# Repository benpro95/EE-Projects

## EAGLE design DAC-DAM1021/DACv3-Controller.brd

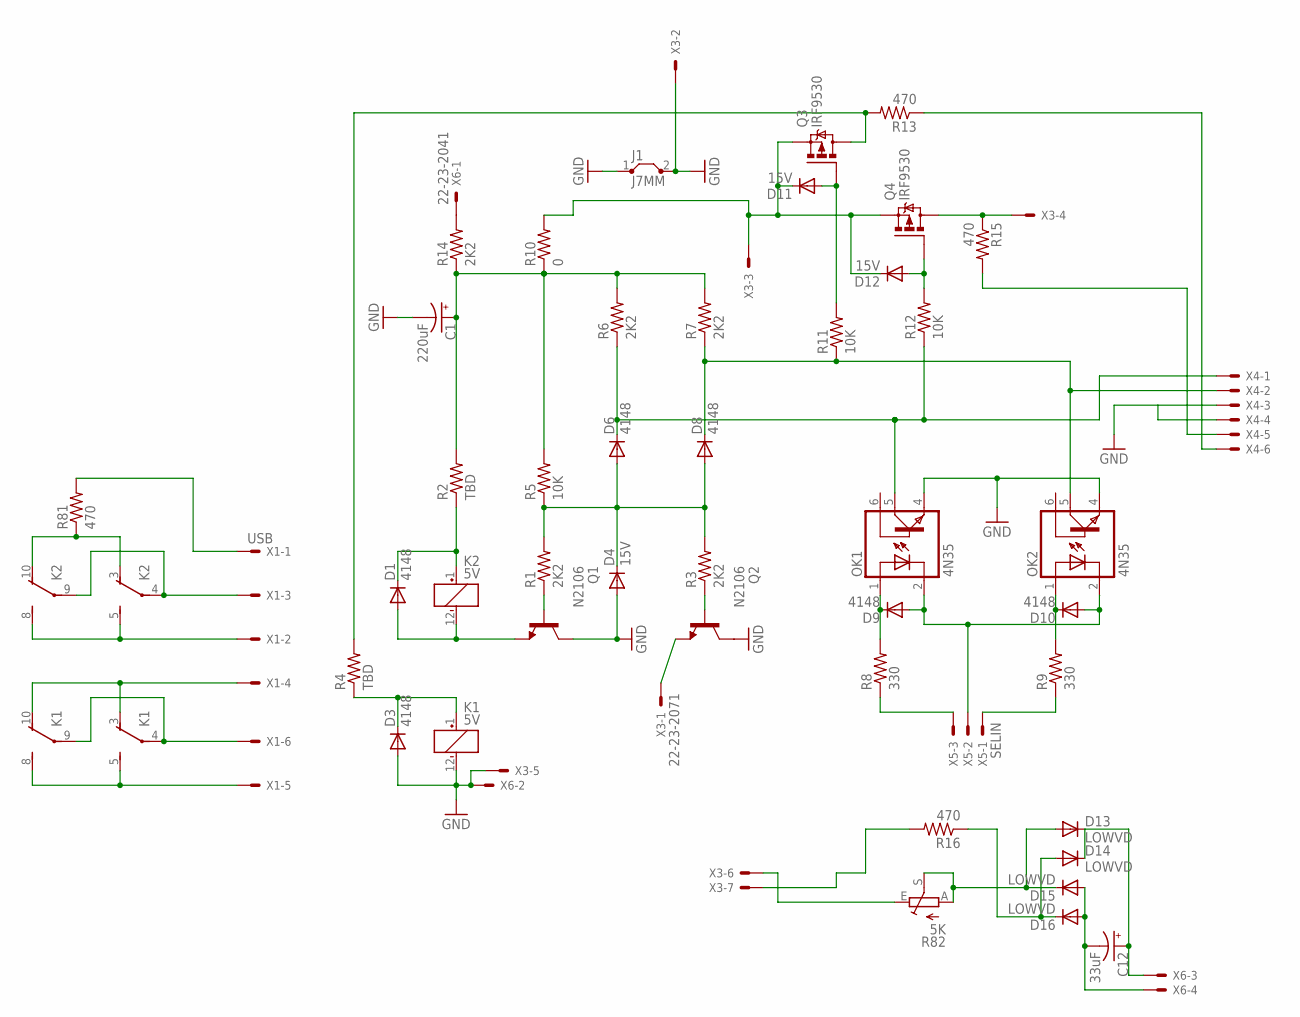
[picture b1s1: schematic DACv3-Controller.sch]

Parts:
C1: 220uF; E5-10,5
C12: 33uF; TAP5-60
D1, D3, D6, D8, D9, D10: 4148; DO35-7
D4, D11, D12: 15V; DO35-7
D13, D14, D15, D16: LOWVD; DO35-7
J1: J7MM; 07
K1, K2: 5V; TX2; MPN TX2-12V
OK1, OK2: 4N35; DIL06
Q1, Q2: N2106; TO92-EBC
Q3, Q4: IRF9530; TO220BV
R1, R3, R6, R7: 2K2; 0207/10
R2, R4: TBD; 0207/10
R5, R11, R12: 10K; 0207/10
R8, R9: 330; 0207/10
R10: 0; 0207/12
R13, R15, R16, R81: 470; 0207/10
R14: 2K2; 0207/12
R82: 5K; RJ9W
X1: USB; 22-23-2061
X3: 22-23-2071
X4: 22-23-2061
X5: SELIN; 22-23-2031
X6: 22-23-2041

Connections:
GND: C1.-, D3.A, D4.A, J1.1, J1.2, K1.12 (-), OK1.4 (EMI), OK2.4 (EMI), Q1.C, Q2.C, X3.2, X3.5, X4.3, X4.4, X6.2
unnamed: K2.4, K2.9, X1.3
unnamed: K2.3 (O), K2.10 (O), R81.1
unnamed: K2.5 (S), K2.8 (S), X1.2
unnamed: R81.2, X1.1
unnamed: K1.4, K1.9, X1.6
unnamed: K1.3 (O), K1.10 (O), X1.4
unnamed: K1.5 (S), K1.8 (S), X1.5
unnamed: D3.C, K1.1 (+), R4.1
unnamed: R8.1, X5.3
unnamed: D1.A, K2.12 (-), Q1.E
unnamed: D1.C, K2.1 (+), R2.1
unnamed: Q1.B, R1.1
unnamed: Q2.B, R3.1
unnamed: D4.C, D6.A, D8.A, R1.2, R3.2, R5.1
unnamed: Q2.E, X3.1
unnamed: D6.C, OK1.5 (COL), R6.1, R12.1, X4.1
unnamed: D8.C, OK2.5 (COL), R7.1, R11.1, X4.2
unnamed: C1.+, R2.2, R5.2, R6.2, R7.2, R10.1, R14.1
unnamed: D9.A, D10.A, OK1.2 (C), OK2.2 (C), X5.2
unnamed: D10.C, OK2.1 (A), R9.2
unnamed: D9.C, OK1.1 (A), R8.2
unnamed: R9.1, X5.1
unnamed: D11.A, Q3.G, R11.2
unnamed: D12.A, Q4.G, R12.2
unnamed: D11.C, D12.C, Q3.S, Q4.S, R10.2, X3.3
unnamed: Q3.D, R4.2, R13.2
unnamed: Q4.D, R15.1, X3.4
unnamed: R15.2, X4.5
unnamed: R13.1, X4.6
unnamed: R82.E, X3.6
unnamed: R16.2, X3.7
unnamed: D14.A, D16.C, R16.1
unnamed: D13.A, D15.C, R82.A, R82.S
unnamed: R14.2, X6.1
unnamed: C12.-, D15.A, D16.A, X6.4
unnamed: C12.+, D13.C, D14.C, X6.3

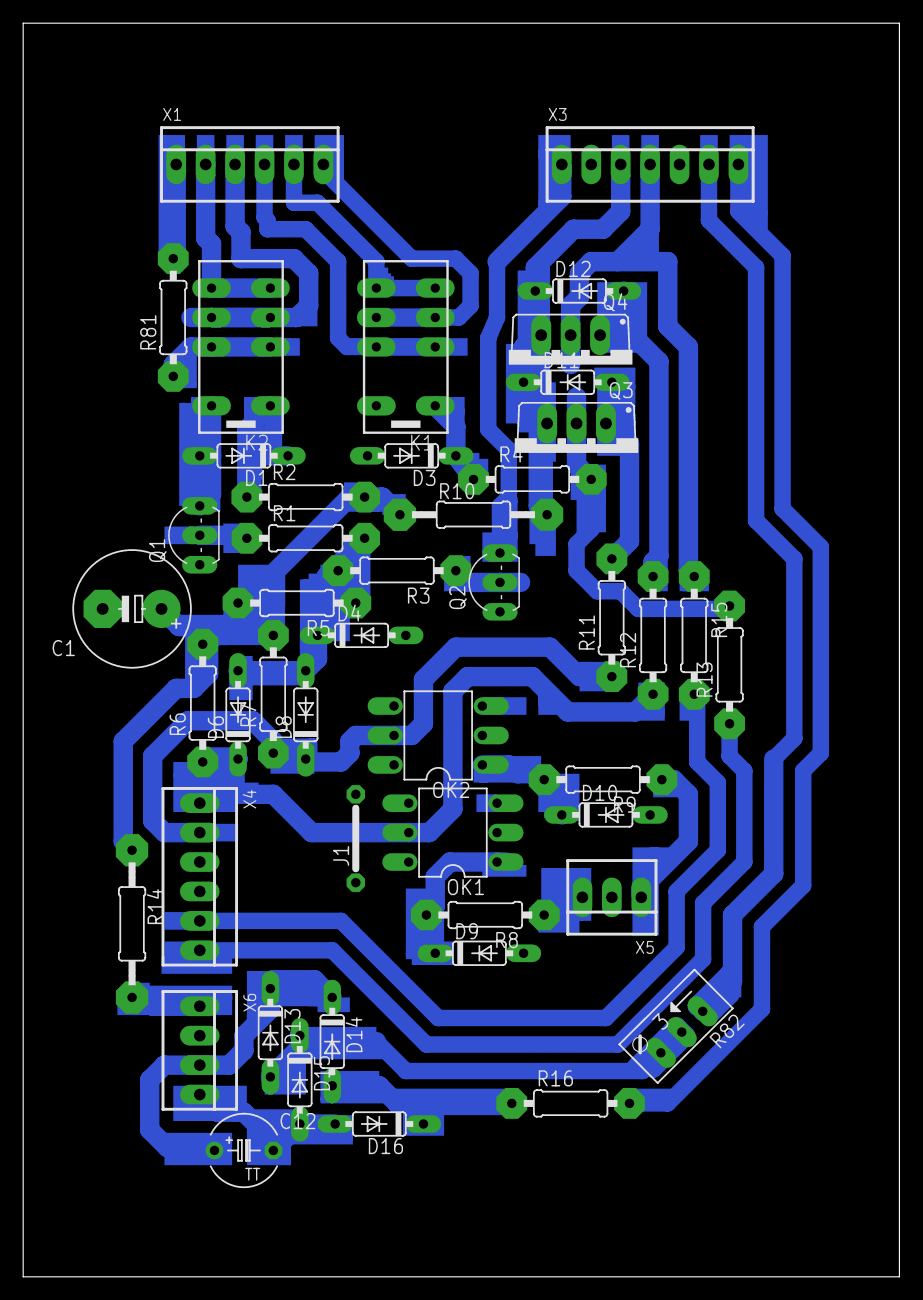
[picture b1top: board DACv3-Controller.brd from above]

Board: 2 copper layers, 75.6 x 108.2 mm, 47 parts (0 on the bottom side), 37 nets.

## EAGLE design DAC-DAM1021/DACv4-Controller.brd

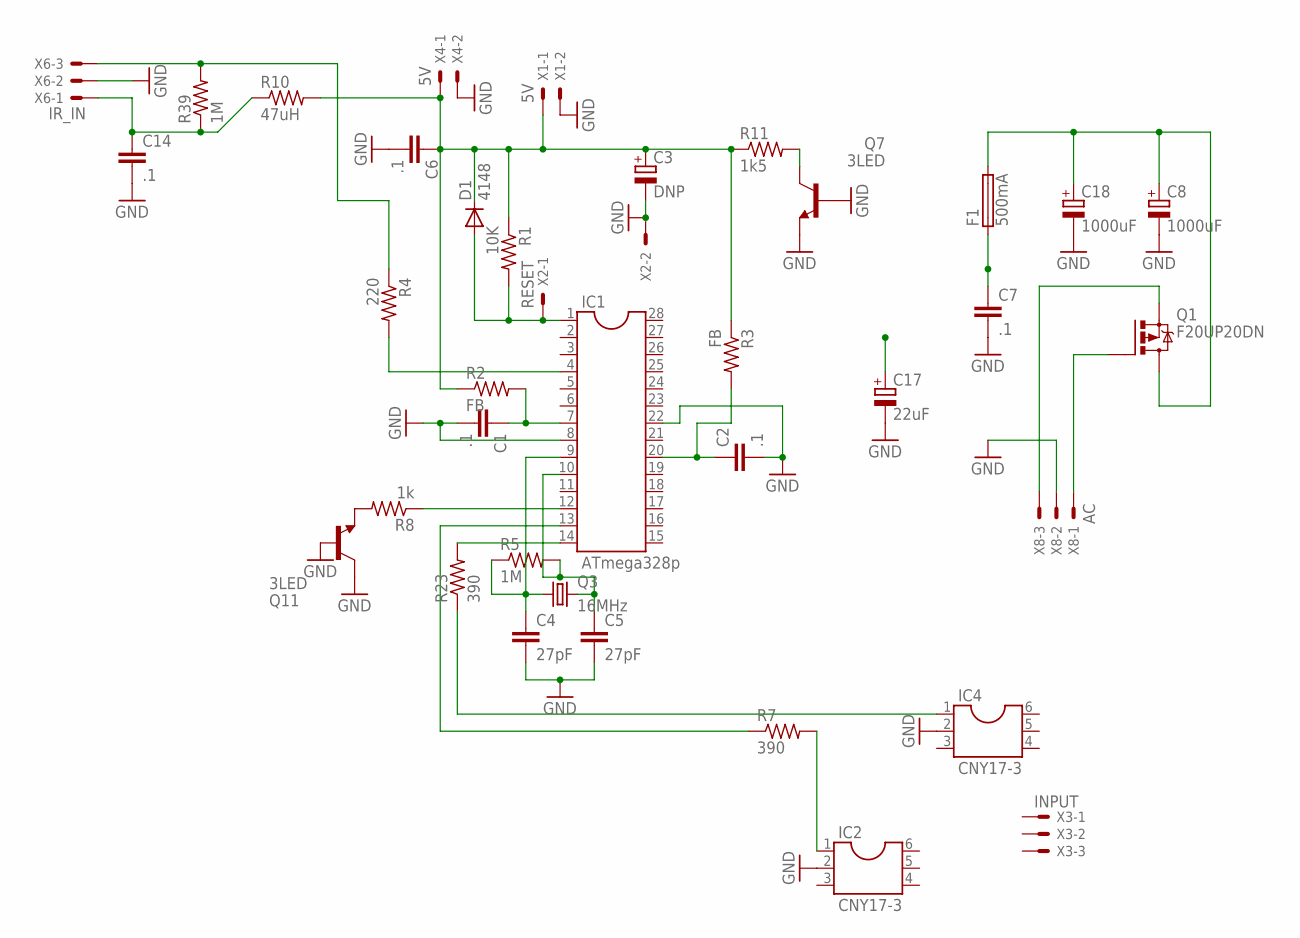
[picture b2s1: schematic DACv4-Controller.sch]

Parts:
C1, C2, C6, C7, C14: .1; C1210K
C3: DNP; E3,5-10
C4, C5: 27pF; C1210K
C8, C18: 1000uF; E5-13
C17: 22uF; E3,5-10
D1: 4148; DO35-7
F1: 500mA; 19560
IC1: ATmega328p; DIL28-3
IC2, IC4: CNY17-3; DIL06
Q1: F20UP20DN; TO220BV
Q3: 16MHz; HC49/S
Q7, Q11: 3LED; TO92-EBC
R1: 10K; 0309/10
R2: FB; 0309/10
R3: FB; 0309/12
R4: 220; 0309/12
R5: 1M; 0309V
R7, R23: 390; 0309/10
R8: 1k; 0204/7
R10: 47uH; 0309/10
R11: 1k5; 0309/12
R39: 1M; 0309/10
X1, X4: 5V; 22-23-2021
X2: RESET; 22-23-2021
X3: INPUT; 22-23-2031
X6: IR_IN; 22-23-2031
X8: AC; 22-23-2031

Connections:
GND: C1.2, C2.2, C3.-, C4.2, C5.2, C6.2, C7.2, C8.-, C14.2, C17.-, C18.-, IC1.8, IC1.22, IC2.2, IC4.2, Q7.B, Q7.E, Q11.B, Q11.C, X1.2, X2.2, X4.2, X6.2, X8.2
unnamed: IC2.1, R7.2
unnamed: D1.A, IC1.1, R1.2, X2.1
unnamed: IC1.4, R4.2
unnamed: C2.1, IC1.20, R3.2
unnamed: R4.1, R39.2, X6.3
unnamed: IC1.13, R7.1
unnamed: IC1.12, R8.1
unnamed: C4.1, IC1.9, Q3.1, R5.1
unnamed: C5.1, IC1.10, Q3.2, R5.2
unnamed: C7.1, F1.1
unnamed: C14.1, R10.1, R39.1, X6.1
unnamed: Q7.C, R11.2
unnamed: C8.+, C18.+, F1.2, Q1.D
unnamed: Q1.S, X8.3
unnamed: Q1.G, X8.1
unnamed: C3.+, C6.1, D1.C, R1.1, R2.1, R3.1, R10.2, R11.1, X1.1, X4.1
unnamed: C1.1, IC1.7, R2.2
unnamed: IC1.14, R23.2
unnamed: IC4.1, R23.1
unnamed: Q11.E, R8.2

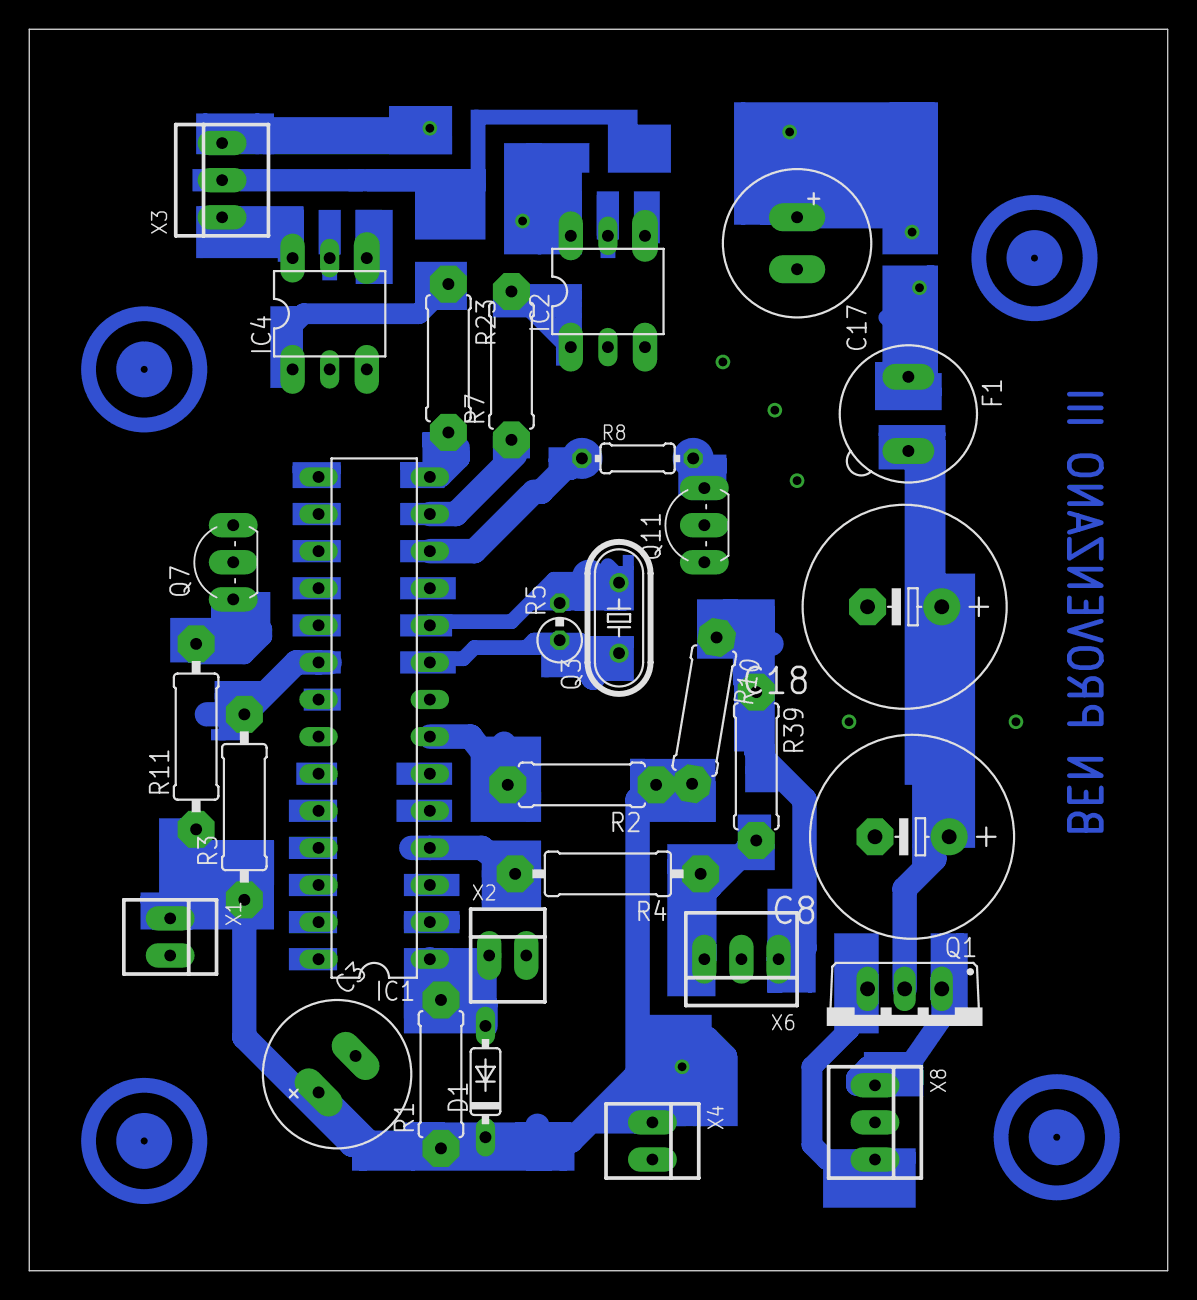
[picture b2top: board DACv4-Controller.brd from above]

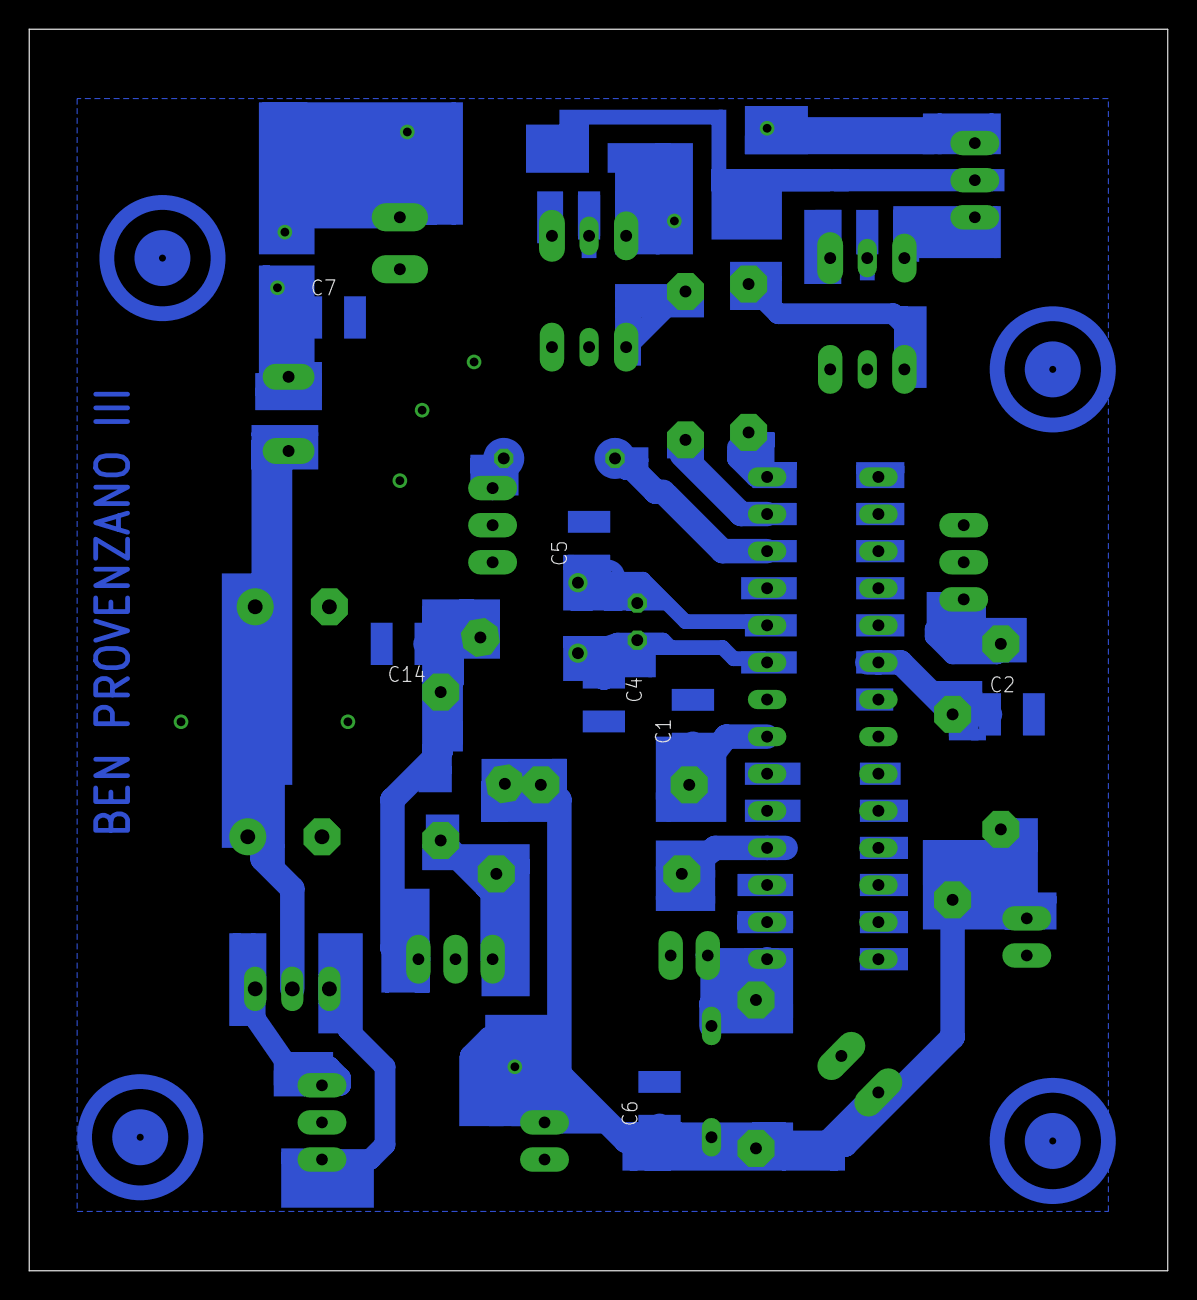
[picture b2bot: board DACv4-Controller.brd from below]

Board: 2 copper layers, 78.0 x 85.0 mm, 37 parts (7 on the bottom side), 21 nets.

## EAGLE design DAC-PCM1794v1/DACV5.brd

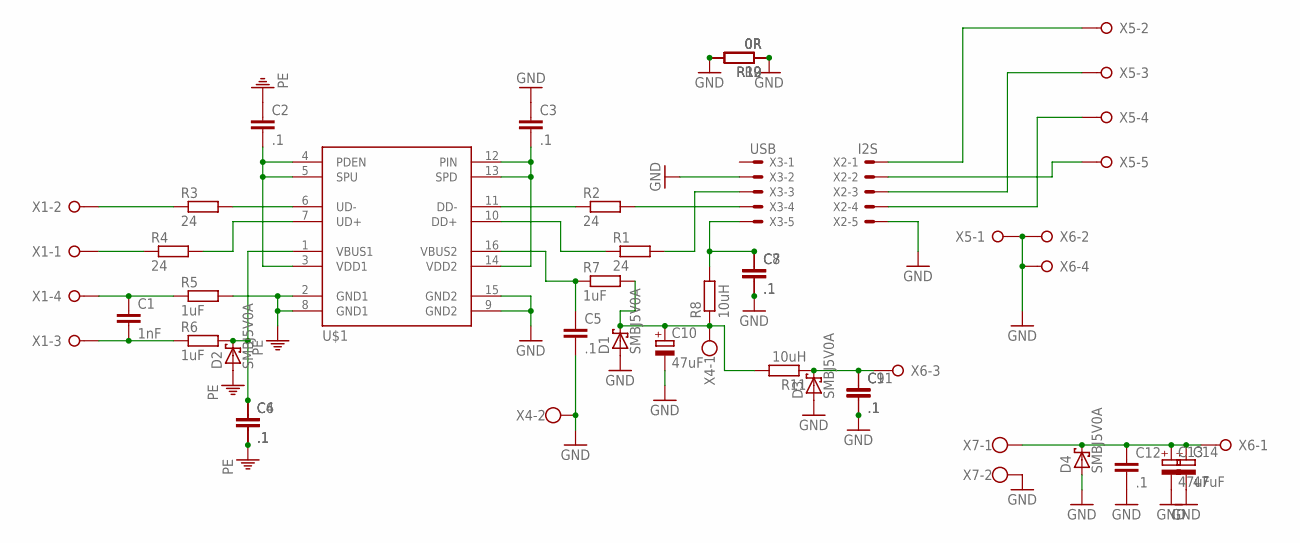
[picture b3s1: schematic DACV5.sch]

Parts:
C1: 1nF; C1210
C2, C3, C4, C5, C6, C7, C8, C9, C11, C12: .1; C1210
C10, C13, C14: 47uF; E5-13
D1, D2, D3, D4: SMBJ5V0A; SMB
R1, R2, R3, R4: 24; R1210
R5, R6, R7: 1uF; R1210
R8, R11: 10uH; 0309/12
R9, R10, R12: 0R; 0309/12
U$1: ADUM4160; SO16W
X1, X6: W237-04P; W237-4P
X2: I2S; 22-23-2051
X3: USB; 22-23-2051
X4: W237-102
X5: W237-05P; W237-5P
X7: W237-102; MPN 237-102

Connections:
GND: C3.1, C5.2, C7.2, C8.2, C9.2, C10.-, C11.2, C12.2, C13.-, C14.-, D1.A, D3.A, D4.A, R9.1, R9.2, R10.1, R10.2, R12.1, R12.2, U$1.9 (GND2), U$1.15 (GND2), X2.5, X3.2, X4.2, X5.1, X6.2, X6.4, X7.2
unnamed: X2.1, X5.2
unnamed: R1.2, X3.3
unnamed: R1.1, U$1.10 (DD+)
unnamed: R4.1, X1.1
unnamed: R3.1, X1.2
unnamed: R2.1, U$1.11 (DD-)
unnamed: R2.2, X3.4
unnamed: R3.2, U$1.6 (UD-)
unnamed: R4.2, U$1.7 (UD+)
unnamed: C1.1, R5.1, X1.4
unnamed: C1.2, R6.1, X1.3
unnamed: C10.+, D1.C, R7.2, R8.1, R11.2, X4.1
unnamed: C7.1, C8.1, R8.2, X3.5
unnamed: X2.3, X5.3
unnamed: X2.2, X5.5
unnamed: X2.4, X5.4
unnamed: C9.1, C11.1, D3.C, R11.1, X6.3
unnamed: C12.1, C13.+, C14.+, D4.C, X6.1, X7.1
PE: C2.1, C4.2, C6.2, D2.A, R5.2, U$1.2 (GND1), U$1.8 (GND1)
VBUS1: C4.1, C6.1, D2.C, R6.2, U$1.1 (VBUS1)
VBUS2: C5.1, R7.1, U$1.16 (VBUS2)
VDD1: C2.2, U$1.3 (VDD1), U$1.4 (PDEN), U$1.5 (SPU)
VDD2: C3.2, U$1.12 (PIN), U$1.13 (SPD), U$1.14 (VDD2)

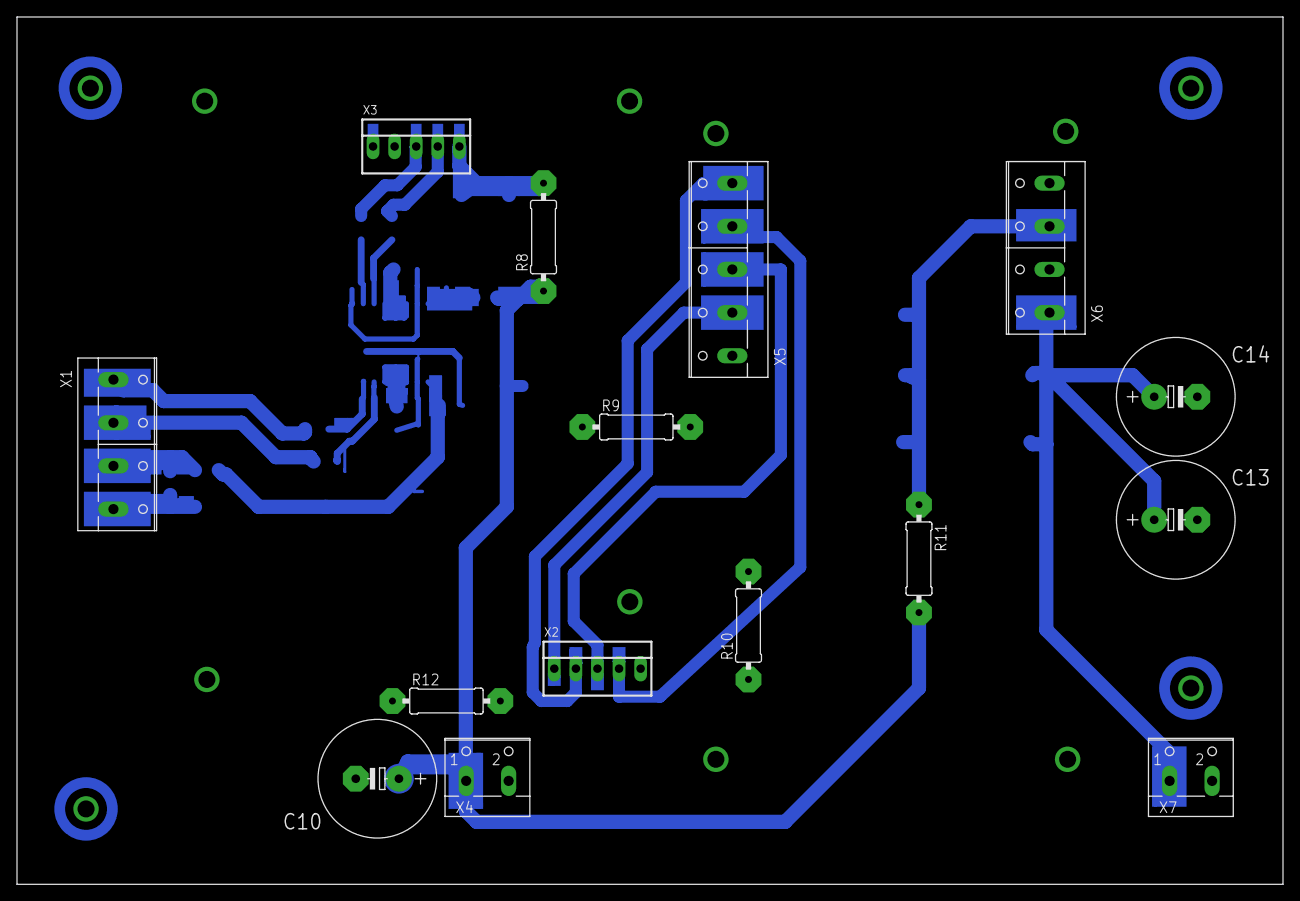
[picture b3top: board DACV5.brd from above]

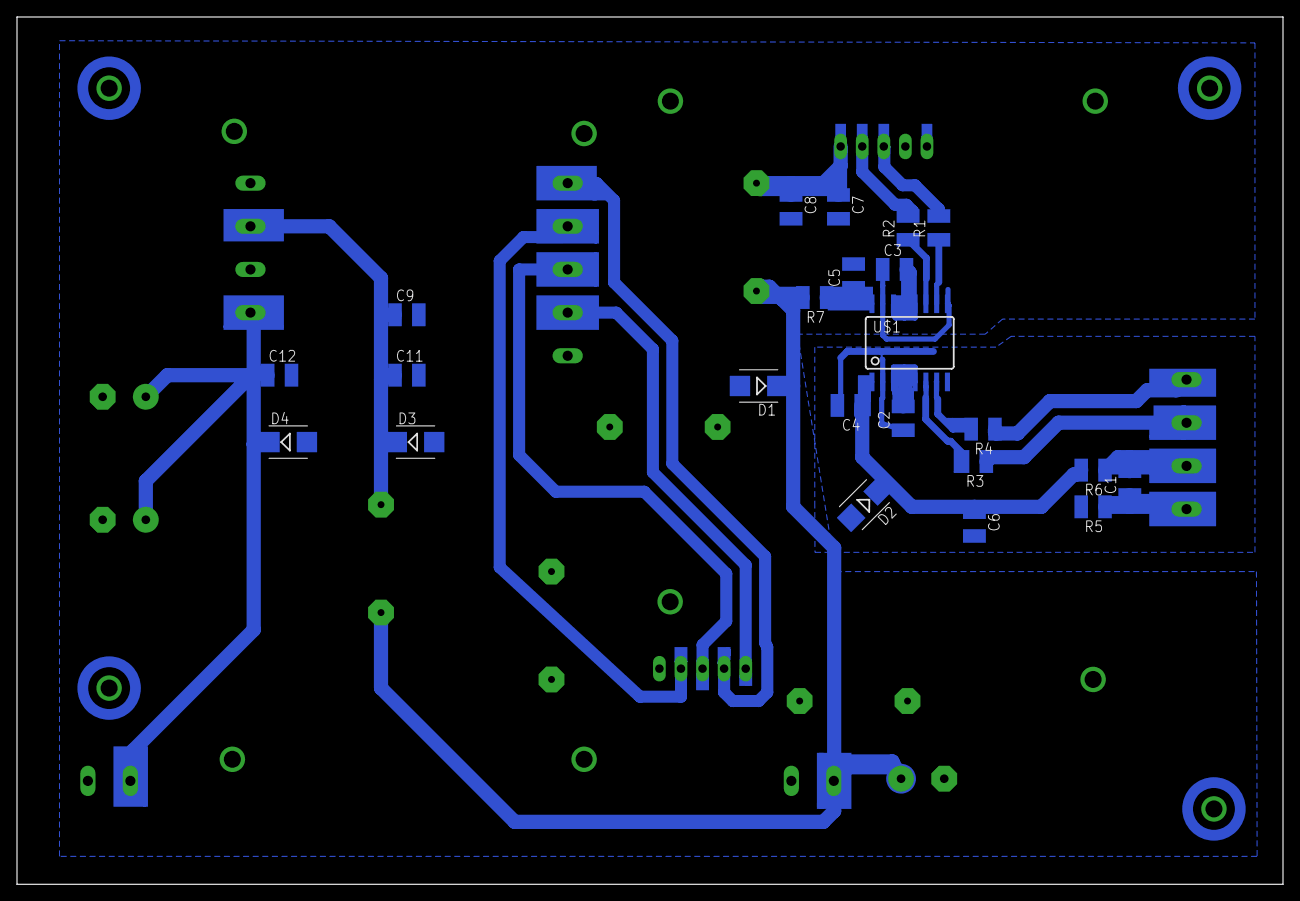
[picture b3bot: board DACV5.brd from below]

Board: 2 copper layers, 149.0 x 102.1 mm, 38 parts (23 on the bottom side), 24 nets.

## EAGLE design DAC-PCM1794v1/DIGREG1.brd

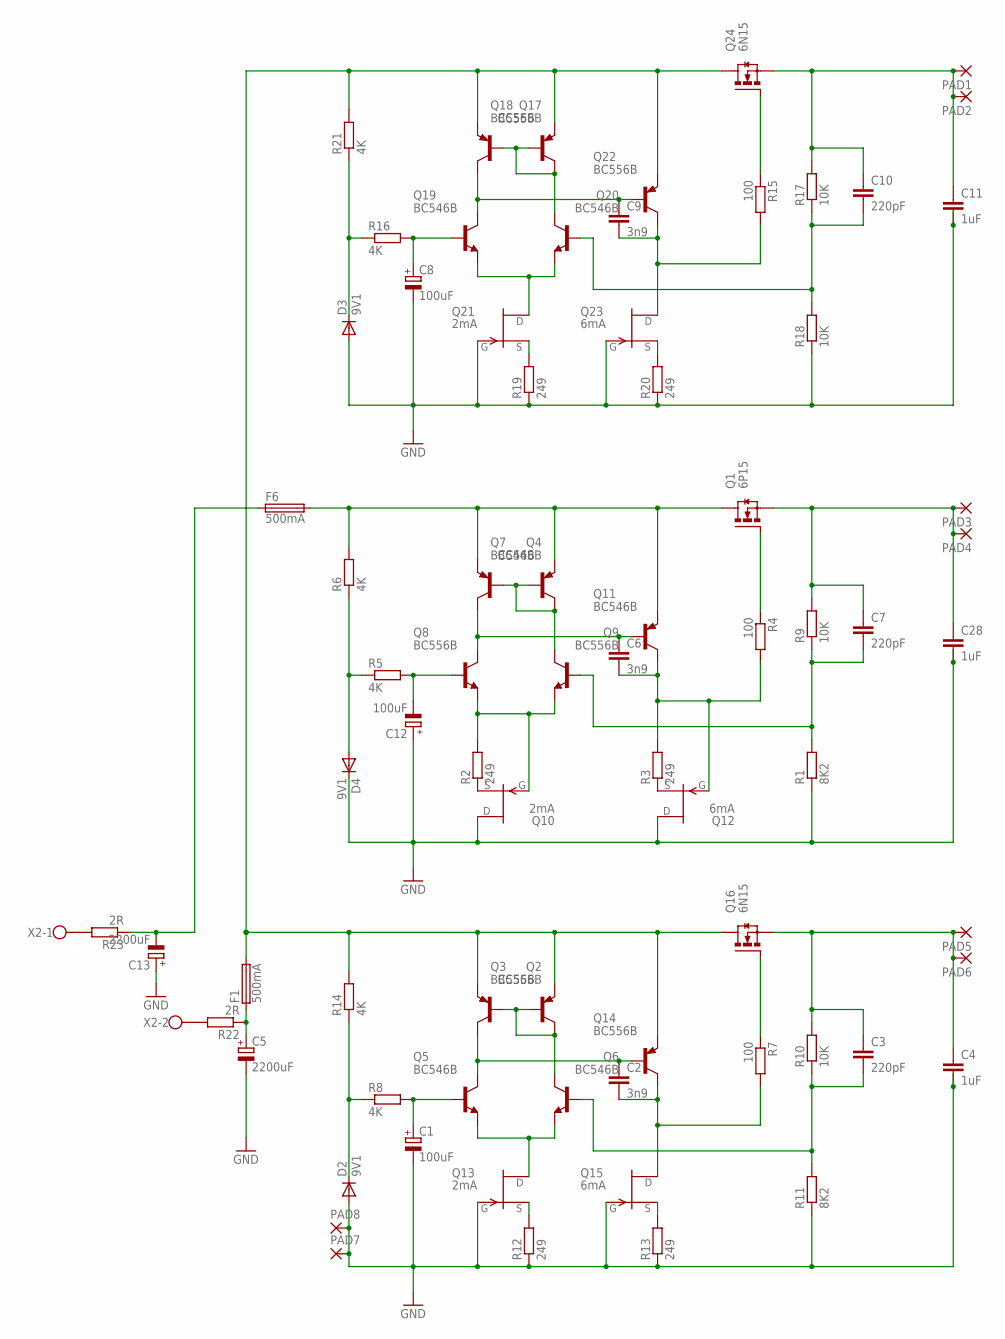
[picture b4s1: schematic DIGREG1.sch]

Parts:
C1, C8, C12: 100uF; E3,5-8
C2, C6, C9: 3n9; C1210K
C3, C7, C10: 220pF; C1210
C4, C11, C28: 1uF; C275-134X316
C5, C13: 2200uF; E7,5-18
D2, D3, D4: 9V1; DO35-7
F1, F6: 500mA; 19560
PAD1, PAD2, PAD3, PAD4, PAD5, PAD6, PAD7, PAD8: 3,81/1,4
Q1: 6P15; TO220BH
Q2, Q3, Q8, Q9, Q14, Q17, Q18, Q22: BC556B; TO92-EBC
Q4, Q5, Q6, Q7, Q11, Q19, Q20: BC546B; TO92-EBC
Q10, Q13, Q21: 2mA; TO92-
Q12, Q15, Q23: 6mA; TO92-
Q16, Q24: 6N15; TO220BH
R1, R11: 8K2; R1210
R2, R3, R12, R13, R19, R20: 249; R1210
R4, R7, R15: 100; 0309/12
R5, R6, R8, R14, R16, R21: 4K; 0309/12
R9, R10, R17, R18: 10K; R1210
R22, R23: 2R; 0309/12
X2: W237-102; MPN 237-102

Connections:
FGD: C1.-, C4.2, C5.-, C8.-, C11.2, C12.+, C13.+, C28.2, D2.A, D3.A, D4.C, PAD7.1, PAD8.1, Q10.3 (D), Q12.3 (D), Q13.1 (G), Q15.1 (G), Q21.1 (G), Q23.1 (G), R1.1, R11.1, R12.1, R13.1, R18.1, R19.1, R20.1
unnamed: D4.A, R5.1, R6.1
unnamed: C7.1, C28.1, PAD3.1, PAD4.1, Q1.S, R9.2
unnamed: Q1.G, R4.1
unnamed: Q12.2 (S), R3.1
unnamed: F6.2, Q1.D, Q4.E, Q7.E, Q11.E, R6.2
unnamed: Q10.2 (S), R2.1
unnamed: C3.1, C4.1, PAD5.1, PAD6.1, Q16.S, R10.2
unnamed: F1.2, Q2.E, Q3.E, Q14.E, Q16.D, Q17.E, Q18.E, Q22.E, Q24.D, R14.2, R21.2
unnamed: C12.-, Q8.B, R5.2
unnamed: Q4.B, Q7.B, Q7.C, Q9.C
unnamed: Q16.G, R7.1
unnamed: C1.+, Q5.B, R8.2
unnamed: Q8.E, Q9.E, Q10.1 (G), R2.2
unnamed: C6.1, Q4.C, Q8.C, Q11.B
unnamed: Q2.B, Q3.B, Q3.C, Q6.C
unnamed: Q5.E, Q6.E, Q13.3 (D)
unnamed: C2.1, Q2.C, Q5.C, Q14.B
unnamed: C6.2, Q11.C, Q12.1 (G), R3.2, R4.2
unnamed: C2.2, Q14.C, Q15.3 (D), R7.2
unnamed: C3.2, Q6.B, R10.1, R11.2
unnamed: C7.2, Q9.B, R1.2, R9.1
unnamed: D2.C, R8.1, R14.1
unnamed: Q13.2 (S), R12.2
unnamed: Q15.2 (S), R13.2
unnamed: C10.1, C11.1, PAD1.1, PAD2.1, Q24.S, R17.2
unnamed: C5.+, F1.1, R22.1
unnamed: Q24.G, R15.1
unnamed: C8.+, Q19.B, R16.2
unnamed: Q17.B, Q18.B, Q18.C, Q20.C
unnamed: Q19.E, Q20.E, Q21.3 (D)
unnamed: C9.1, Q17.C, Q19.C, Q22.B
unnamed: C9.2, Q22.C, Q23.3 (D), R15.2
unnamed: C10.2, Q20.B, R17.1, R18.2
unnamed: D3.C, R16.1, R21.1
unnamed: Q21.2 (S), R19.2
unnamed: Q23.2 (S), R20.2
unnamed: R22.2, X2.2
unnamed: R23.2, X2.1
unnamed: C13.-, F6.1, R23.1

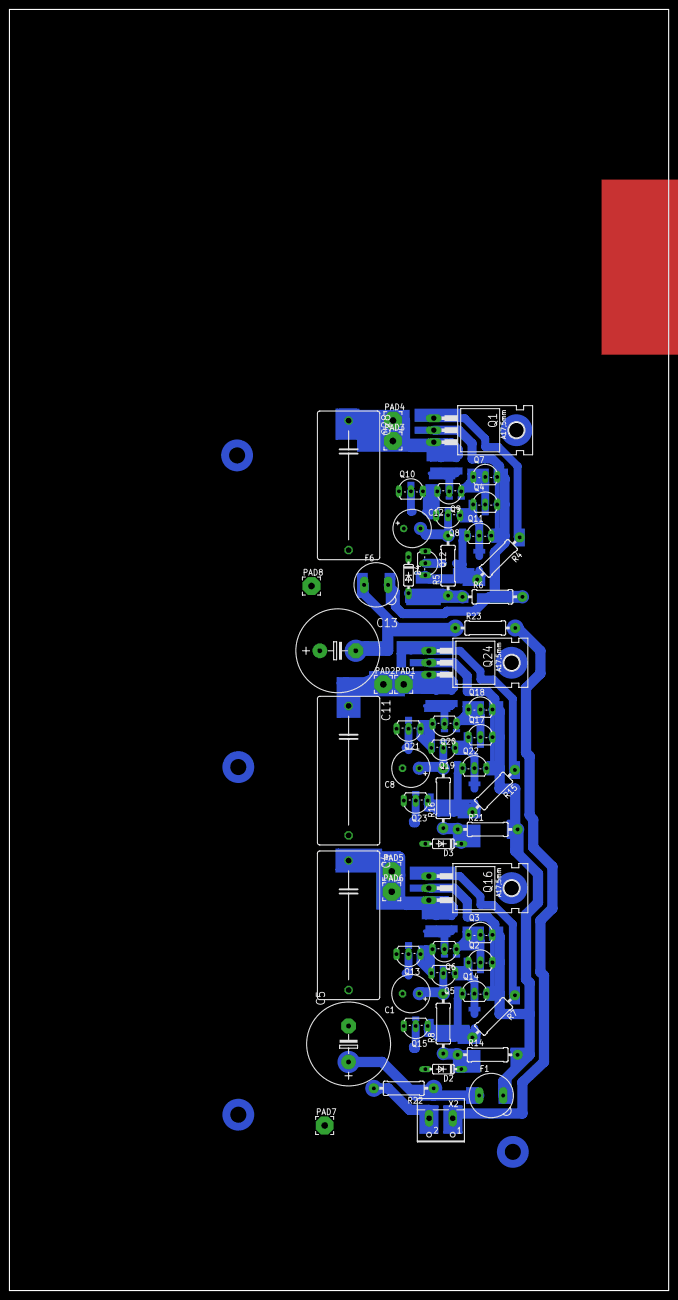
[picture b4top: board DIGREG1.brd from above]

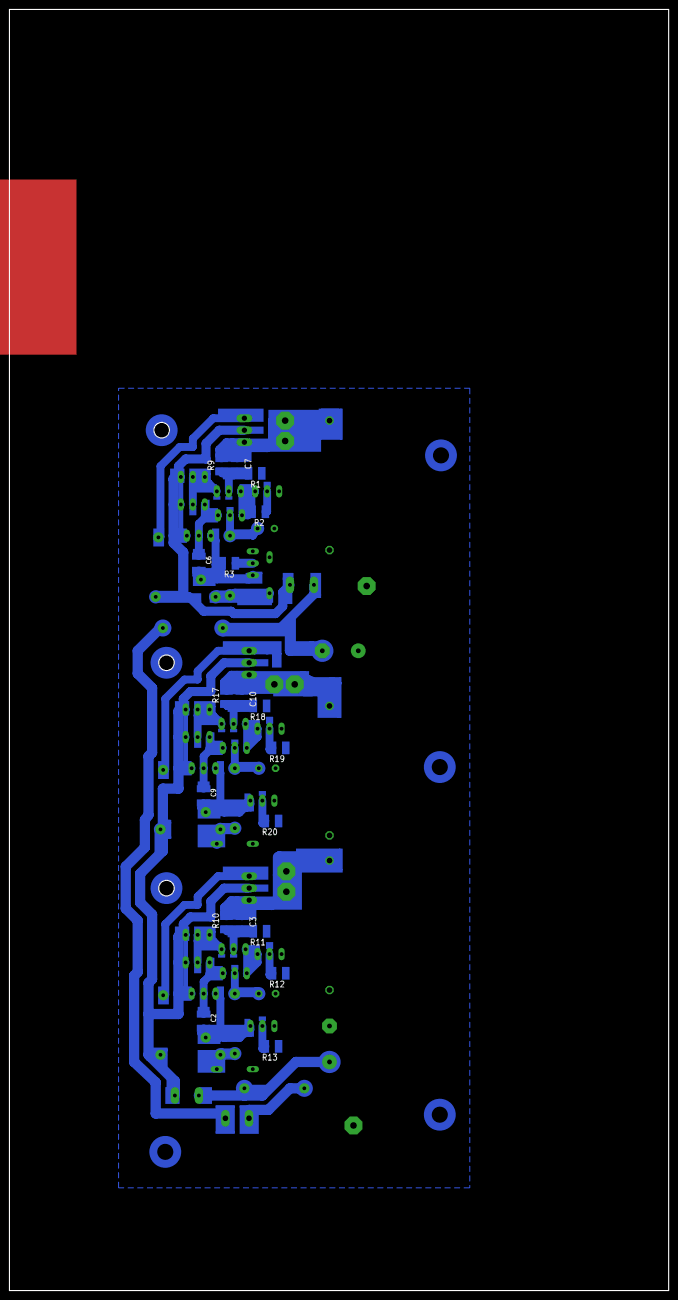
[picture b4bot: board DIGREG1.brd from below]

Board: 2 copper layers, 139.7 x 271.5 mm, 75 parts (18 on the bottom side), 40 nets.

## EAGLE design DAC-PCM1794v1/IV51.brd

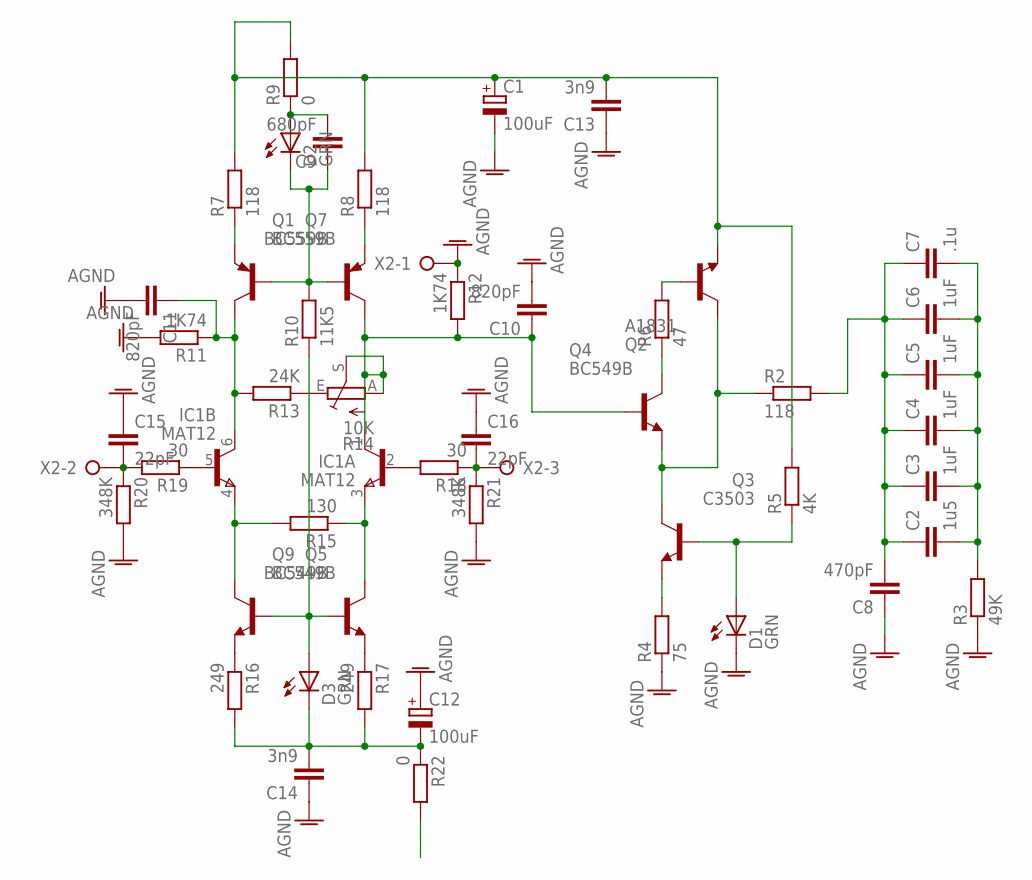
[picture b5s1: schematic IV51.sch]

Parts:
C1, C12: 100uF; E5-10,5
C2: 1u5; C275-134X316
C3, C4, C5, C6: 1uF; C275-134X316
C7: .1u; C050-075X075
C8: 470pF; C102-043X133
C9: 680pF; C050-045X075
C10, C11: 820pF; C075-032X103
C13, C14: 3n9; C1210
C15, C16: 22pF; C075-032X103
D1, D2, D3: GRN; SFH482
IC1: MAT12; TO78
Q1, Q7: BC559B; TO92-EBC
Q2: A1831; TO126
Q3: C3503; TO126
Q4, Q5, Q9: BC549B; TO92-EBC
R2, R7, R8: 118; 0309/12
R3: 49K; 0309/12
R4: 75; 0309/12
R5: 4K; 0309/12
R6: 47; 0309/12
R9, R22: 0; 0309/12
R10: 11K5; 0309/12
R11, R12: 1K74; 0309/12
R13: 24K; 0309/12
R14: 10K; RJ9W
R15: 130; 0309/12
R16, R17: 249; R2010
R18, R19: 30; 0309/12
R20, R21: 348K; R1210
X2: W237-3E

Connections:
AGND: C1.-, C8.1, C10.2, C11.2, C12.+, C13.1, C14.1, C15.1, C16.1, D1.K (C), R3.1, R4.1, R11.2, R12.1, R20.2, R21.2, X2.1
unnamed: Q7.E, R7.1
unnamed: C2.1, C3.1, C4.1, C5.1, C6.1, C7.1, C8.2, R2.2
unnamed: D1.A, Q3.3 (B), R5.1
unnamed: C9.2, D2.A, R9.1
unnamed: Q2.3 (B), R6.2
unnamed: Q2.2 (C), Q3.2 (C), Q4.E, R2.1
unnamed: Q3.1 (E), R4.2
unnamed: C1.+, C13.2, Q2.1 (E), R5.2, R7.2, R8.2, R9.2
unnamed: Q4.C, R6.1
unnamed: Q1.E, R8.1
unnamed: C10.1, IC1.1 (C), Q1.C, Q4.B, R12.2, R14.A, R14.S
unnamed: C11.1, IC1.6 (C), Q7.C, R11.1, R13.2
unnamed: C9.1, D2.K (C), Q1.B, Q7.B, R10.2
unnamed: R13.1, R14.E
unnamed: IC1.4 (E), Q5.C, R15.2
unnamed: IC1.3 (E), Q9.C, R15.1
unnamed: Q5.E, R16.1
unnamed: Q9.E, R17.1
unnamed: C12.-, C14.2, D3.K (C), R16.2, R17.2, R22.1
unnamed: D3.A, Q5.B, Q9.B, R10.1
unnamed: IC1.2 (B), R18.2
unnamed: IC1.5 (B), R19.1
unnamed: C15.2, R19.2, R20.1, X2.2
unnamed: C16.2, R18.1, R21.1, X2.3
OUT: C2.2, C3.2, C4.2, C5.2, C6.2, C7.2, R3.2

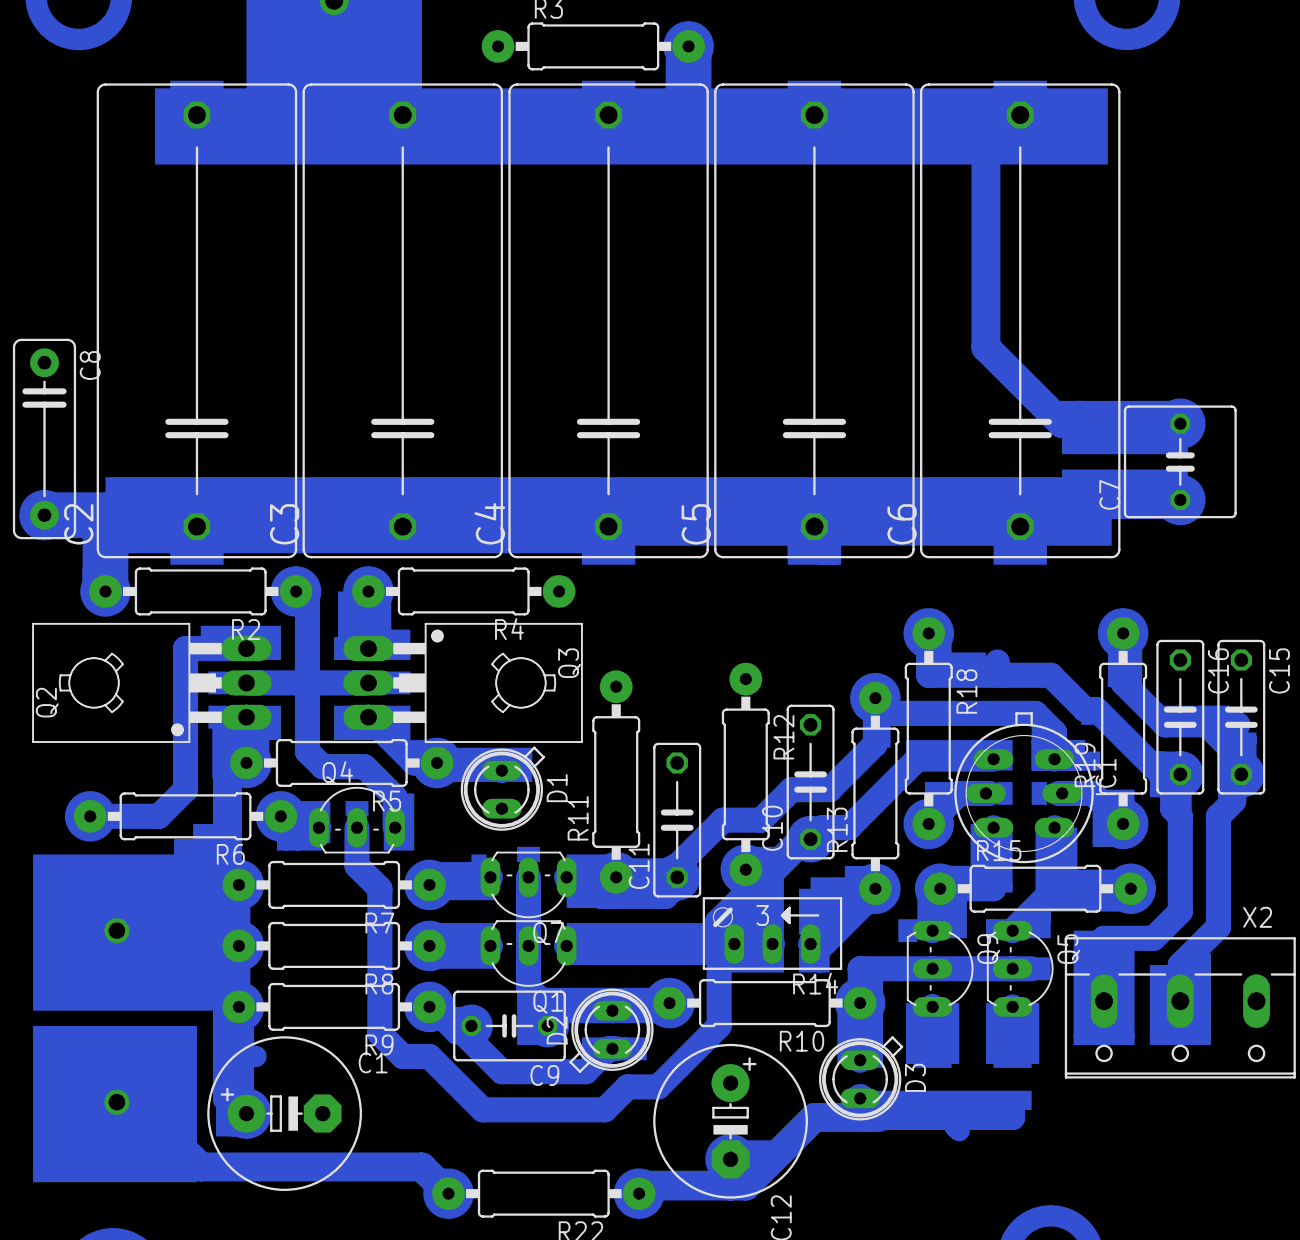
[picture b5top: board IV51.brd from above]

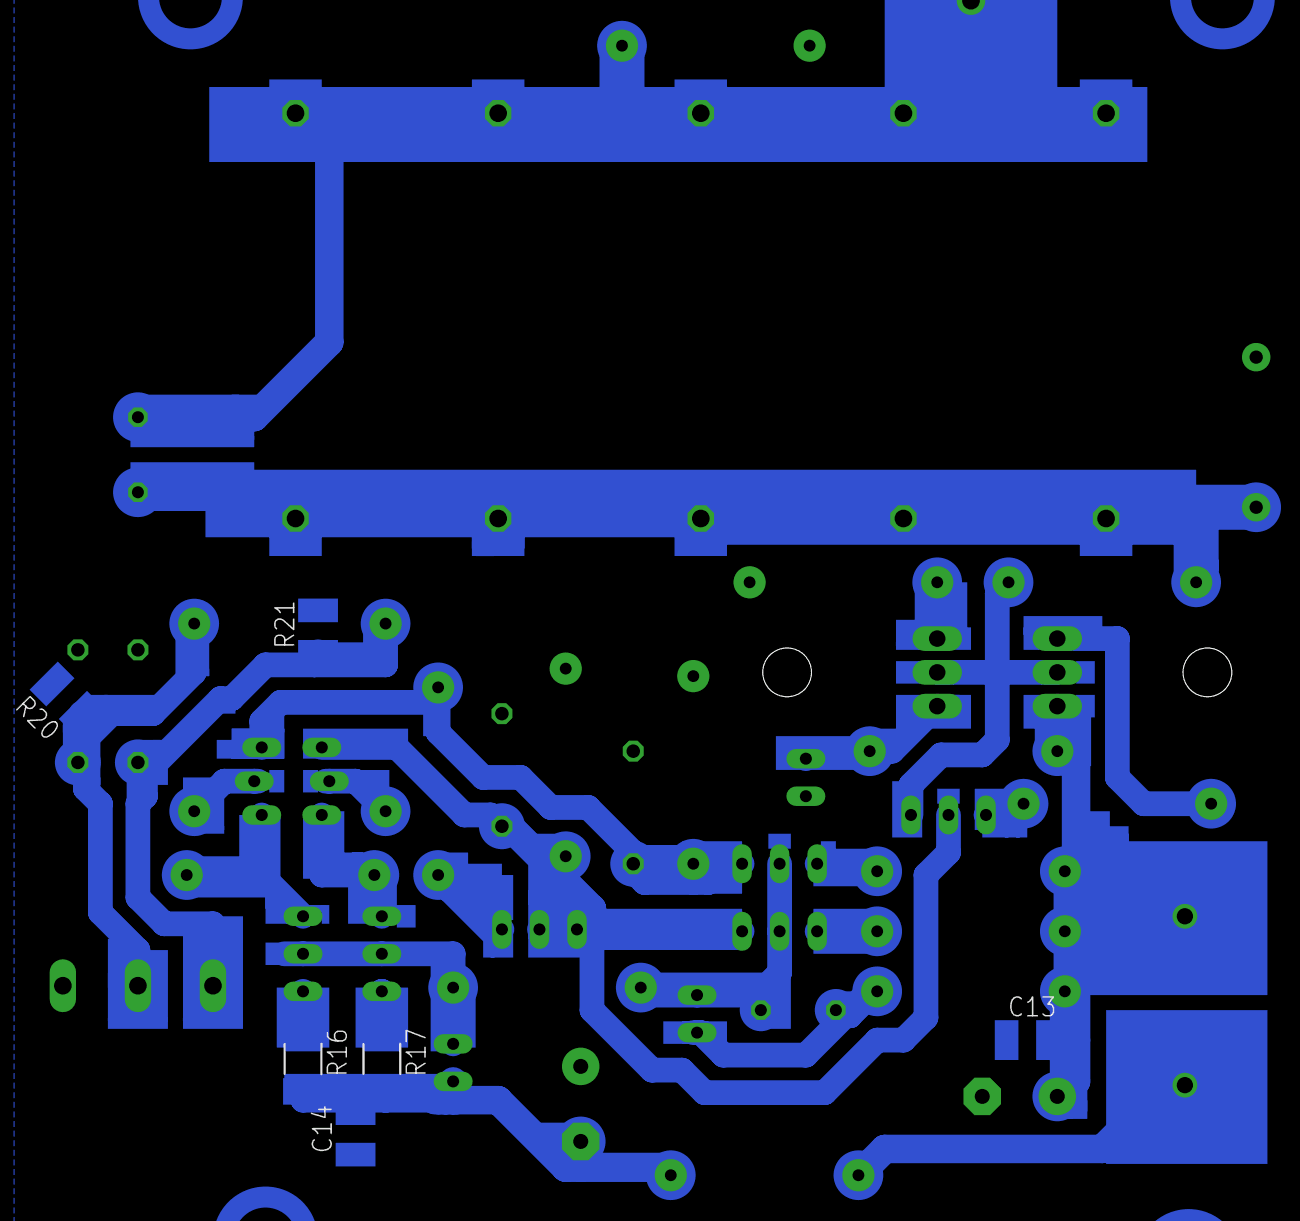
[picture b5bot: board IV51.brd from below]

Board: 2 copper layers, 49 parts (6 on the bottom side), 26 nets.
